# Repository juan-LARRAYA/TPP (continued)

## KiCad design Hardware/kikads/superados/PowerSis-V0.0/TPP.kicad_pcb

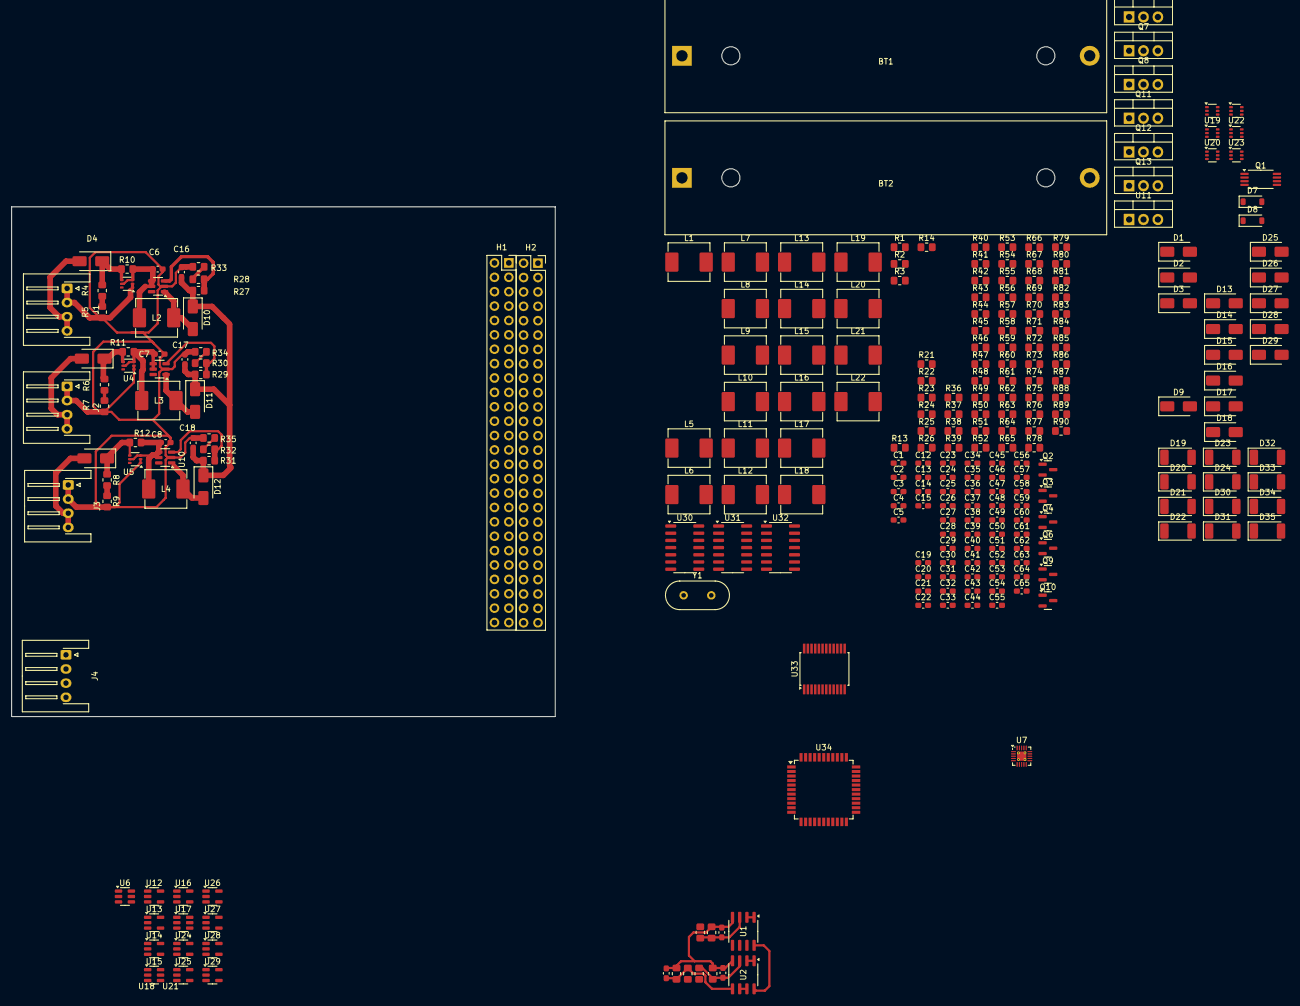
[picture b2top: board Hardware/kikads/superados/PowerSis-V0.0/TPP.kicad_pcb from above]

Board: 2 copper layers, 96.0 x 90.0 mm, 268 parts (0 on the bottom side), 169 nets.

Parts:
BT1, BT2: Battery_Cell; BatteryHolder_MPD_BH-18650-PC2
C1, C2, C3, C4, C5, C15, C19, C20, C21, C22, C23, C24, C25, C26, C27, C28, C29, C30, C31, C44, C45, C46, C47, C48, C49: 100nF; C_0603_1608Metric_Pad1.08x0.95mm_HandSolder
C6, C7, C8, C9, C10, C11, C12, C16, C17, C18, C32, C33, C34, C35, C36, C37, C38, C39, C40, C41, C42, C43: 22uF; C_0603_1608Metric_Pad1.08x0.95mm_HandSolder
C13, C14: 1uF; C_0603_1608Metric_Pad1.08x0.95mm_HandSolder
C50, C51, C52, C53, C54, C55, C56, C57, C58, C59, C60, C61: 10pF; C_0603_1608Metric_Pad1.08x0.95mm_HandSolder
C62, C63, C64, C65: 22pF; C_0603_1608Metric_Pad1.08x0.95mm_HandSolder
D1, D2, D3, D4, D5, D6, D9, D10, D11, D12, D13, D14, D15, D16, D17, D18, D25, D26, D27, D28, D29: CRS08; D_SMA
D7, D8: 1N4148W; D_SOD-123
D19, D20, D21, D22, D23, D24, D30, D31, D32, D33, D34, D35: SMZxxx; D_MELF
H1, H2: Conn_02x26_Odd_Even; PinSocket_2x26_P2.54mm_Vertical
J1, J2, J3, J4: Conn_01x04; JST_XH_S4B-XH-A-1_1x04_P2.50mm_Horizontal
L1, L5, L6, L7, L8, L9, L10: 220uH; L_Abracon_ASPI-0630LR
L2, L3, L4, L11, L12: 22uH; L_Abracon_ASPI-0630LR
L13, L14, L15, L16: 4.7uH; L_Abracon_ASPI-0630LR
L17, L18, L19, L20, L21, L22: 10uH; L_Abracon_ASPI-0630LR
Q1: RU8205G; TSSOP-8_4.4x3mm_P0.65mm
Q2, Q3, Q4, Q6, Q9, Q10: BC817; SOT-23
Q5, Q7, Q8, Q11, Q12, Q13: Q_PMOS_DGS; TO-220-3_Vertical
R1, R2, R3, R22, R26, R36, R38, R42, R44, R46, R48, R55, R56, R57, R58, R59, R60, R61, R62, R63, R64, R65, R66, R67, R68, R69, R70, R71, R72, R73, R74, R75, R76, R77, R78, R79, R80, R81, R82, R83, R84, R85, R86, R87, R88, R89, R90: 1K5; R_0805_2012Metric_Pad1.20x1.40mm_HandSolder
R4, R5, R6, R7, R8, R9, R21, R37: 56K; R_0805_2012Metric_Pad1.20x1.40mm_HandSolder
R10, R11, R12, R49, R50, R51, R52, R53, R54: Rcs; R_0805_2012Metric_Pad1.20x1.40mm_HandSolder
R13, R24: 100; R_0805_2012Metric_Pad1.20x1.40mm_HandSolder
R14: 0.1; R_0805_2012Metric_Pad1.20x1.40mm_HandSolder
R15, R16, R17, R27, R29, R31: 180k; R_0805_2012Metric_Pad1.20x1.40mm_HandSolder
R18, R19, R20, R28, R30, R32, R33, R34, R35: 10k; R_0805_2012Metric_Pad1.20x1.40mm_HandSolder
R23, R25: 0.47; R_0805_2012Metric_Pad1.20x1.40mm_HandSolder
R39: 220K; R_0805_2012Metric_Pad1.20x1.40mm_HandSolder
R40: 1K1; R_0805_2012Metric_Pad1.20x1.40mm_HandSolder
R41, R43, R45, R47: 110K; R_0805_2012Metric_Pad1.20x1.40mm_HandSolder
U1, U2: LM358; SOIC-8_3.9x4.9mm_P1.27mm
U3, U4, U5, U18, U19, U20, U21, U22, U23: INA199xxDCK; SOT-363_SC-70-6
U6, U8, U9, U10, U15, U17: MT3608; SOT-23-6
U7: BQ76905; QFN-20-1EP_3x3mm_P0.4mm_EP1.65x1.65mm_ThermalVias
U11: LM7805_TO220; TO-220-3_Vertical
U12, U13, U14, U16: LM2831YMF; SOT-23-5
U24, U25, U26, U27, U28, U29: SN74LVC1G14DBV; SOT-23-5
U30, U31, U32: 4011; SOIC-14_3.9x8.7mm_P1.27mm
U33: CD74HC4067SM; SSOP-24_5.3x8.2mm_P0.65mm
U34: ATmega1284P-P; TQFP-44_10x10mm_P0.8mm
Y1: Crystal; Crystal_HC49-U_Vertical

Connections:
+3.3V: C58.2, D19.1 (K), H2.27, L19.2
+3.3V Bis: C61.2, D23.1 (K), H2.28, L22.2
+5V: C60.2, D24.1 (K), H2.25, L21.2, R81.1
+5V Bis: C56.2, D21.1 (K), H2.26, L17.2, R82.1
+8V_Aux: C12.1, C15.2, D9.1 (K), R21.1, U11.1 (VI)
+12V: C57.2, D20.1 (K), H1.47, L18.2, R80.1
+24V: C59.2, D22.1 (K), H1.49, L20.2, R79.1
Alert: U7.14 (ALERT), U34.24 (PC2)
Aux +5V: U18.3 (V+), U19.3 (V+), U20.3 (V+), U21.3 (V+), U22.3 (V+), U23.3 (V+), U24.5 (VCC), U25.5 (VCC), U26.5 (VCC), U27.5 (VCC), U28.5 (VCC), U29.5 (VCC), U30.14 (VDD), U31.14 (VDD), U32.14 (VDD)
Batery + In: BT1.1 (+), C16.1, C17.1, C18.1, D7.2 (A), D8.2 (A), D10.1 (K), D11.1 (K), D12.1 (K), H2.45, H2.46, R1.1, R27.1, R29.1, R31.1
Batery + Out: C20.2, C21.2, C22.2, C23.2, C24.2, C25.2, L5.1, L6.1, L7.1, L8.1, L9.1, L10.1
Batery -: BT2.2 (-), C1.1, C4.1, C9.2, C10.2, C11.2, C62.1, C63.1, C64.1, C65.1, R3.1, R13.2, R14.2, R18.2, R19.2, R20.2, U1.4 (V-), U2.4 (V-), U7.11 (VSS), U33.12 (GND), U34.11 (GND), U34.31 (GND)
Batery_middle: BT1.2 (-), BT2.1 (+), R2.1
Enable_+3.3V: U13.4 (EN), U34.16 (PD2)
Enable_+3.3V_Bis: U16.4 (EN), U34.17 (PD3)
Enable_+5V: U12.4 (EN), U34.14 (PD0)
Enable_+5V_Bis: U14.4 (EN), U34.15 (PD1)
Enable_+12V: U17.4 (EN), U34.29 (PC7)
Enable_+24V: U15.4 (EN), U34.28 (PC6)
GND: C3.2, C6.2, C7.2, C8.2, C12.2, C13.1, C14.1, C15.1, C16.2, C17.2, C18.2, C19.1, C20.1, C21.1, C22.1, C23.1, C24.1, C25.1, C26.1, C27.1, C28.1, C29.1, C30.1, C31.1, C32.2, C33.2, C34.2, C35.2, C36.2, C37.2, C38.2, C39.2, C40.2, C41.2, C42.2, C43.2, C44.1, C45.1, C46.1, C47.1, C48.1, C49.1, C50.1, C51.1, C52.1, C53.1, C54.1, C55.1, C56.1, C57.1, C58.1, C59.1, C60.1, C61.1, D13.2 (A), D14.2 (A), D15.2 (A), D17.2 (A), D19.2 (A), D20.2 (A), D21.2 (A), D22.2 (A), D23.2 (A), D24.2 (A), D30.2 (A), D31.2 (A), D32.2 (A), D33.2 (A), D34.2 (A), D35.2 (A), H2.29, H2.30, H2.31, H2.32, J1.1, J1.2, J2.1, J2.2, J3.1, J3.2, J4.1, Q1.2 (D1), Q1.3 (D1), Q2.2 (E), Q3.2 (E), Q4.2 (E), Q6.2 (E), Q9.2 (E), Q10.2 (E), R5.2, R7.2, R9.2, R22.2, R33.2, R34.2, R35.2, R36.2, R38.2, R40.2, R42.2, R44.2, R46.2, R48.2, R85.2, R86.2, R87.2, R88.2, R89.2, R90.2, U3.1 (REF), U3.2 (GND), U4.1 (REF), U4.2 (GND), U5.1 (REF), U5.2 (GND), U6.2 (GND), U8.2 (GND), U9.2 (GND), U10.2 (GND), U11.2 (GND), U12.2 (GND), U13.2 (GND), U14.2 (GND), U15.2 (GND), U16.2 (GND), U17.2 (GND), U18.1 (REF), U18.2 (GND), U19.1 (REF), U19.2 (GND), U20.1 (REF), U20.2 (GND), U21.1 (REF), U21.2 (GND), U22.1 (REF), U22.2 (GND), U23.1 (REF), U23.2 (GND), U24.3 (GND), U25.3 (GND), U26.3 (GND), U27.3 (GND), U28.3 (GND), U29.3 (GND), U30.7 (VSS), U31.7 (VSS), U32.7 (VSS)
MPPT_X_Control: R15.1, U34.19 (PD5)
MPPT_X_Current_Sense: U3.6, U33.9 (I0)
MPPT_X_Voltage_Sense: R4.2, R5.1, U33.8 (I1)
MPPT_Y_Control: R16.1, U34.20 (PD6)
MPPT_Y_Current_Sense: U4.6, U33.7 (I2)
MPPT_Y_Voltage_Sense: R6.2, R7.1, U33.6 (I3)
MPPT_Z_Control: R17.1, U34.21 (PD7)
MPPT_Z_Current_Sense: U5.6, U33.5 (I4)
MPPT_Z_Voltage_Sense: R8.2, R9.1, U33.4 (I5)
unnamed: C44.2, R55.1, U30.6
unnamed: C45.2, R56.1, U31.6
unnamed: C46.2, R57.1, U32.6
unnamed: C47.2, R58.1, U30.13
unnamed: C48.2, R59.1, U31.13
unnamed: C49.2, R60.1, U32.13
unnamed: C3.1, D1.1 (K), D2.1 (K), D3.1 (K), L1.1, U1.8 (V+), U2.8 (V+), U6.4 (EN), U6.5 (IN)
unnamed: D4.1 (K), R4.1, R10.1, U3.4 (+)
unnamed: D5.1 (K), R6.1, R11.1, U4.4 (+)
unnamed: D6.1 (K), R8.1, R12.1, U5.4 (+)
unnamed: D7.1 (K), R23.1
unnamed: D8.1 (K), R25.1
unnamed: D9.2 (A), L1.2, U6.1 (SW)
unnamed: D10.2 (A), L2.2, U8.1 (SW)
unnamed: D11.2 (A), L3.2, U9.1 (SW)
unnamed: D12.2 (A), L4.2, U10.1 (SW)
unnamed: D13.1 (K), L13.1, U13.1 (SW)
unnamed: D14.1 (K), L14.1, U12.1 (SW)
unnamed: D15.1 (K), L15.1, U14.1 (SW)
unnamed: D16.2 (A), L11.2, U15.1 (SW)
unnamed: C42.1, D16.1 (K), R37.1, R51.1, U20.4 (+)
unnamed: D17.1 (K), L16.1, U16.1 (SW)
unnamed: D18.2 (A), L12.2, U17.1 (SW)
unnamed: C43.1, D18.1 (K), R39.1, R54.1, U23.4 (+)
unnamed: D30.1 (K), R79.2, R90.1, U33.3 (I6)
unnamed: D31.1 (K), R80.2, R89.1, U33.2 (I7)
unnamed: D32.1 (K), R81.2, R88.1, U33.23 (I8)
unnamed: D33.1 (K), R82.2, R87.1, U33.22 (I9)
unnamed: D34.1 (K), R83.2, R86.1, U33.21 (I10)
unnamed: D35.1 (K), R84.2, R85.1, U33.20 (I11)
unnamed: Q1.4 (G1), R36.1, U7.10 (CHG)
unnamed: Q1.5 (G2), R26.1, U7.9 (DSG)
unnamed: Q1.1 (S1/D2), Q1.8 (S1/D2)
unnamed: Q1.6 (S2), Q1.7 (S2), R14.1, R24.2, R26.2
unnamed: Q2.1 (B), R62.2
unnamed: Q2.3 (C), R73.2
unnamed: Q3.1 (B), R64.2
unnamed: Q3.3 (C), R74.2
unnamed: Q4.1 (B), R66.2
unnamed: Q4.3 (C), R75.2
unnamed: C54.2, L21.1, Q5.1 (D)
unnamed: Q5.2 (G), R61.2, R73.1
unnamed: Q5.3 (S), R49.2, R61.1, U18.5 (-)
unnamed: Q6.1 (B), R69.2
unnamed: Q6.3 (C), R76.2
unnamed: C52.2, L19.1, Q7.1 (D)
unnamed: Q7.2 (G), R63.2, R74.1
unnamed: Q7.3 (S), R50.2, R63.1, U19.5 (-)
unnamed: C53.2, L20.1, Q8.1 (D)
unnamed: Q8.2 (G), R65.2, R75.1
unnamed: Q8.3 (S), R51.2, R65.1, U20.5 (-)
unnamed: Q9.1 (B), R71.2
unnamed: Q9.3 (C), R77.2
unnamed: Q10.1 (B), R72.2
unnamed: Q10.3 (C), R78.2
unnamed: C50.2, L17.1, Q11.1 (D)
unnamed: Q11.2 (G), R67.2, R76.1
unnamed: Q11.3 (S), R52.2, R67.1, U21.5 (-)
unnamed: C55.2, L22.1, Q12.1 (D)
unnamed: Q12.2 (G), R68.2, R77.1
unnamed: Q12.3 (S), R53.2, R68.1, U22.5 (-)
unnamed: C51.2, L18.1, Q13.1 (D)
unnamed: Q13.2 (G), R70.2, R78.1
unnamed: Q13.3 (S), R54.2, R70.1, U23.5 (-)
unnamed: R55.2, R62.1, U30.2, U30.4
unnamed: R56.2, R64.1, U31.2, U31.4
unnamed: R57.2, R66.1, U32.2, U32.4
unnamed: R58.2, R69.1, U30.9, U30.11
unnamed: R59.2, R71.1, U31.9, U31.11
unnamed: R60.2, R72.1, U32.9, U32.11
unnamed: C9.1, R15.2, R18.1, U1.3 (+)
unnamed: R28.2, R33.1, U1.1, U1.2 (-)
unnamed: C11.1, R17.2, R20.1, U2.3 (+)
unnamed: R32.2, R35.1, U2.1, U2.2 (-)
unnamed: C10.1, R16.2, R19.1, U2.5 (+)
unnamed: R30.2, R34.1, U2.6 (-), U2.7
unnamed: C6.1, L2.1, R10.2, U3.3 (V+), U3.5 (-), U8.4 (EN), U8.5 (IN)
unnamed: C7.1, L3.1, R11.2, U4.3 (V+), U4.5 (-), U9.4 (EN), U9.5 (IN)
unnamed: R21.2, R22.1, U6.3 (FB)
unnamed: C14.2, R25.2, U7.16 (BAT)
unnamed: C13.2, R23.2, U7.17 (REGSRC)
unnamed: C5.1, R13.1, U7.6 (SRN)
unnamed: C5.2, R24.1, U7.7 (SRP)
unnamed: C4.2, R3.2, U7.5 (VC0)
unnamed: C1.2, C2.1, R2.2, U7.1 (VC3A), U7.2 (VC3B), U7.3 (VC2), U7.4 (VC1), U7.19 (VC4A), U7.20 (VC4B)
unnamed: C2.2, R1.2, U7.18 (VC5)
unnamed: R27.2, R28.1, U8.3 (FB)
unnamed: R29.2, R30.1, U9.3 (FB)
unnamed: C8.1, L4.1, R12.2, U5.3 (V+), U5.5 (-), U10.4 (EN), U10.5 (IN)
unnamed: R31.2, R32.1, U10.3 (FB)
unnamed: R41.2, R42.1, U12.3 (FB)
unnamed: C27.2, C32.1, L6.2, U12.5 (VIN)
unnamed: R43.2, R44.1, U13.3 (FB)
unnamed: C26.2, C33.1, L5.2, U13.5 (VIN)
unnamed: R45.2, R46.1, U14.3 (FB)
unnamed: C28.2, C36.1, L7.2, U14.5 (VIN)
unnamed: R37.2, R38.1, U15.3 (FB)
unnamed: C31.2, C34.1, L10.2, L11.1, U15.5 (IN)
unnamed: R47.2, R48.1, U16.3 (FB)
unnamed: C29.2, C37.1, L8.2, U16.5 (VIN)
unnamed: R39.2, R40.1, U17.3 (FB)
unnamed: C30.2, C35.1, L9.2, L12.1, U17.5 (IN)
unnamed: C39.1, L14.2, R41.1, R49.1, U18.4 (+)
unnamed: U18.6, U24.2
unnamed: C38.1, L13.2, R43.1, R50.1, U19.4 (+)
unnamed: U19.6, U25.2
unnamed: U20.6, U26.2
unnamed: C40.1, L15.2, R45.1, R52.1, U21.4 (+)
unnamed: U21.6, U27.2
unnamed: C41.1, L16.2, R47.1, R53.1, U22.4 (+)
unnamed: U22.6, U28.2
unnamed: U23.6, U29.2
unnamed: U24.4, U30.1
unnamed: U25.4, U31.1
unnamed: U26.4, U32.1
unnamed: U27.4, U30.8
unnamed: U28.4, U31.8
unnamed: U29.4, U32.8
unnamed: U33.1 (COM), U34.40 (PA0)
unnamed: U33.10 (S0), U34.39 (PA1)
unnamed: U33.11 (S1), U34.38 (PA2)
unnamed: U33.14 (S2), U34.37 (PA3)
unnamed: U33.13 (S3), U34.36 (PA4)
unnamed: U33.15 (~E), U34.35 (PA5)
unnamed: C64.2, U34.13 (XTAL1), Y1.1
unnamed: C65.2, U34.12 (XTAL2), Y1.2
Ov_Current_+3.3V: U31.3, U31.5, U34.5 (PB4)
Ov_Current_+3.3V_Bis: U31.10, U31.12, U34.6 (PB5)
Ov_Current_+5V: U30.3, U30.5, U34.3 (PB2)
Ov_Current_+5V_Bis: U30.10, U30.12, U34.4 (PB3)
Ov_Current_+12V: U32.10, U32.12, U34.2 (PB1)
Ov_Current_+24V: U32.3, U32.5, U34.1 (PB0)
SCL: H1.41, U7.12 (SCL), U34.23 (PC1)
SDA: H1.43, U7.13 (SDA), U34.22 (PC0)
VccMCU: C62.2, C63.2, D25.1 (K), D26.1 (K), D27.1 (K), D28.1 (K), D29.1 (K), U33.24 (VCC), U34.9 (~RESET), U34.10 (VCC), U34.30 (AVCC)
VregAux: C19.2, D29.2 (A), U11.3 (VO)
Vregout: D28.2 (A), U7.15 (REGOUT)
X_X´_Solar_Cell: D1.2 (A), D4.2 (A), D25.2 (A), J1.3, J1.4
Y_Y´_Solar_Cell: D2.2 (A), D5.2 (A), D26.2 (A), J2.3, J2.4
Z_Z´_Solar_Cell: D3.2 (A), D6.2 (A), D27.2 (A), J3.3, J3.4

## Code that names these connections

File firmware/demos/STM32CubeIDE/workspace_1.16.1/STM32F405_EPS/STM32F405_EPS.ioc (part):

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Mcu.Name=STM32F405RGTx
Mcu.Package=LQFP64
Mcu.UserName=STM32F405RGTx
PA0-WKUP.GPIOParameters=GPIO_Label
PA0-WKUP.GPIO_Label=MPPTYControl
PA0-WKUP.Signal=S_TIM2_CH1_ETR
PA1.GPIOParameters=GPIO_Label
PA1.GPIO_Label=CurrZMPPT
PA1.Signal=ADCx_IN1
PA11.GPIOParameters=GPIO_Label
PA11.GPIO_Label=USB D-
PA11.Mode=Device_Only
PA11.Signal=USB_OTG_FS_DM
PA12.GPIOParameters=GPIO_Label
PA12.GPIO_Label=USB D+
PA12.Mode=Device_Only
PA12.Signal=USB_OTG_FS_DP
PA13.GPIOParameters=GPIO_Label
PA13.GPIO_Label=SWDIO
PA13.Mode=Serial_Wire
PA13.Signal=SYS_JTMS-SWDIO
PA14.GPIOParameters=GPIO_Label
PA14.GPIO_Label=SWCLK
PA14.Mode=Serial_Wire
PA14.Signal=SYS_JTCK-SWCLK
PA2.GPIOParameters=GPIO_Label
PA2.GPIO_Label=VoltZMPPT
PA2.Signal=ADCx_IN2
PA3.GPIOParameters=GPIO_Label
PA3.GPIO_Label=MPPTZControl
PA3.Signal=S_TIM5_CH4
PA4.GPIOParameters=GPIO_Label
PA4.GPIO_Label=Curr5VBis
PA4.Signal=ADCx_IN4
PA5.GPIOParameters=GPIO_Label
PA5.GPIO_Label=Volt5VBis
PA5.Signal=ADCx_IN5
PA6.GPIOParameters=GPIO_Label
PA6.GPIO_Label=Volt3.3V
PA6.Signal=ADCx_IN6
PA7.GPIOParameters=GPIO_Label
PA7.GPIO_Label=Curr3.3V
PA7.Signal=ADCx_IN7
PA8.GPIOParameters=GPIO_Label
PA8.GPIO_Label=SCL-Sat
PA8.Mode=I2C
PA8.Signal=I2C3_SCL
PB0.GPIOParameters=GPIO_Label
PB0.GPIO_Label=Volt3.3VBis
PB0.Signal=ADCx_IN8
PB1.GPIOParameters=GPIO_Label
PB1.GPIO_Label=Curr3.3Vbis
PB1.Signal=ADCx_IN9
PB10.GPIOParameters=GPIO_Label
PB10.GPIO_Label=Enable3.3VBis
PB10.Signal=GPIO_Output
PB11.GPIOParameters=GPIO_Label
PB11.GPIO_Label=Enable3.3V
PB11.Signal=GPIO_Output
PB12.GPIOParameters=GPIO_Label
PB12.GPIO_Label=Enable5VBis
PB12.Signal=GPIO_Output
PB14.GPIOParameters=GPIO_Label
PB14.GPIO_Label=CalEnable
PB14.Signal=GPIO_Output
PB2.GPIOParameters=GPIO_Label
PB2.GPIO_Label=Enable5V
PB2.Signal=GPIO_Output
PB6.GPIOParameters=GPIO_Label
PB6.GPIO_Label=SCL-BMS
PB6.Mode=I2C
PB6.Signal=I2C1_SCL
PB7.GPIOParameters=GPIO_Label
PB7.GPIO_Label=SDA-BMS
PB7.Mode=I2C
PB7.Signal=I2C1_SDA
PB8.GPIOParameters=GPIO_Label
PB8.GPIO_Label=BMS-Alert
PB8.Signal=GPIO_Input
PB9.GPIOParameters=GPIO_Label
PB9.GPIO_Label=MPPTXControl
PB9.Signal=S_TIM4_CH4
PC0.GPIOParameters=GPIO_Label
PC0.GPIO_Label=CurrXMPPT
PC0.Signal=ADCx_IN10
PC1.GPIOParameters=GPIO_Label
PC1.GPIO_Label=VoltXMPPT
PC1.Signal=ADCx_IN11
PC10.GPIOParameters=GPIO_Label
PC10.GPIO_Label=TX
PC10.Mode=Asynchronous
PC10.Signal=UART4_TX
PC11.GPIOParameters=GPIO_Label
PC11.GPIO_Label=RX
PC11.Mode=Asynchronous
PC11.Signal=UART4_RX
PC2.GPIOParameters=GPIO_Label
PC2.GPIO_Label=CurrYMPPT
PC2.Signal=ADCx_IN12
PC3.GPIOParameters=GPIO_Label
PC3.GPIO_Label=VoltYMPPT
PC3.Signal=ADCx_IN13
PC4.GPIOParameters=GPIO_Label
PC4.GPIO_Label=Volt5V
PC4.Signal=ADCx_IN14
PC5.GPIOParameters=GPIO_Label
PC5.GPIO_Label=Curr5V
PC5.Signal=ADCx_IN15
PC9.GPIOParameters=GPIO_Label
PC9.GPIO_Label=SDA-Sat
PC9.Mode=I2C
PC9.Signal=I2C3_SDA
PH0-OSC_IN.Mode=HSE-External-Oscillator
PH0-OSC_IN.Signal=RCC_OSC_IN
PH1-OSC_OUT.Mode=HSE-External-Oscillator
PH1-OSC_OUT.Signal=RCC_OSC_OUT
RCC.HSE_VALUE=8000000
RCC.SYSCLKFreq_VALUE=168000000
RCC.SYSCLKSource=RCC_SYSCLKSOURCE_PLLCLK
board=custom

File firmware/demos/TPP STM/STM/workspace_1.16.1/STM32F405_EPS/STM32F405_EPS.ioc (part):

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Mcu.Name=STM32F405RGTx
Mcu.Package=LQFP64
Mcu.UserName=STM32F405RGTx
PA0-WKUP.GPIOParameters=GPIO_Label
PA0-WKUP.GPIO_Label=MPPTYControl
PA0-WKUP.Signal=S_TIM2_CH1_ETR
PA1.GPIOParameters=GPIO_PuPd,GPIO_Label,GPIO_Mode
PA1.GPIO_Label=MPPZ_CUR
PA1.GPIO_Mode=GPIO_MODE_ANALOG
PA1.GPIO_PuPd=GPIO_NOPULL
PA1.Signal=ADCx_IN1
PA13.GPIOParameters=GPIO_Label
PA13.GPIO_Label=SWDIO
PA13.Mode=Serial_Wire
PA13.Signal=SYS_JTMS-SWDIO
PA14.GPIOParameters=GPIO_Label
PA14.GPIO_Label=SWCLK
PA14.Mode=Serial_Wire
PA14.Signal=SYS_JTCK-SWCLK
PA2.GPIOParameters=GPIO_PuPd,GPIO_Label,GPIO_Mode
PA2.GPIO_Label=MPPZ_VOL
PA2.GPIO_Mode=GPIO_MODE_ANALOG
PA2.GPIO_PuPd=GPIO_NOPULL
PA2.Signal=ADCx_IN2
PA3.GPIOParameters=GPIO_Label
PA3.GPIO_Label=MPPTZControl
PA3.Signal=S_TIM5_CH4
PA4.GPIOParameters=GPIO_PuPd,GPIO_Label,GPIO_Mode
PA4.GPIO_Label=CUR_5BIS
PA4.GPIO_Mode=GPIO_MODE_ANALOG
PA4.GPIO_PuPd=GPIO_NOPULL
PA4.Signal=ADCx_IN4
PA5.GPIOParameters=GPIO_PuPd,GPIO_Label,GPIO_Mode
PA5.GPIO_Label=VOL_5BIS
PA5.GPIO_Mode=GPIO_MODE_ANALOG
PA5.GPIO_PuPd=GPIO_NOPULL
PA5.Signal=ADCx_IN5
PA6.GPIOParameters=GPIO_PuPd,GPIO_Label,GPIO_Mode
PA6.GPIO_Label=VOL_3.3V
PA6.GPIO_Mode=GPIO_MODE_ANALOG
PA6.GPIO_PuPd=GPIO_NOPULL
PA6.Signal=ADCx_IN6
PA7.GPIOParameters=GPIO_PuPd,GPIO_Label,GPIO_Mode
PA7.GPIO_Label=CUR_3.3V
PA7.GPIO_Mode=GPIO_MODE_ANALOG
PA7.GPIO_PuPd=GPIO_NOPULL
PA7.Signal=ADCx_IN7
PA8.GPIOParameters=GPIO_Label,GPIO_Pu
PA8.GPIO_Label=SCL_I2C_COM
PA8.GPIO_Pu=GPIO_PULLUP
PA8.Mode=I2C
PA8.Signal=I2C3_SCL
PA9.GPIOParameters=GPIO_PuPd,GPIO_Label
PA9.GPIO_Label=EnableBatOut
PA9.GPIO_PuPd=GPIO_PULLUP
PA9.Signal=GPIO_Output
PB0.GPIOParameters=GPIO_Label
PB0.GPIO_Label=CELL_MENOS
PB0.Signal=ADCx_IN8
PB11.GPIOParameters=GPIO_PuPd,GPIO_Label
PB11.GPIO_Label=Enable3.3V
PB11.GPIO_PuPd=GPIO_PULLUP
PB11.Signal=GPIO_Output
PB12.GPIOParameters=GPIO_PuPd,GPIO_Label
PB12.GPIO_Label=Enable5VBis
PB12.GPIO_PuPd=GPIO_PULLUP
PB12.Signal=GPIO_Output
PB14.GPIOParameters=GPIO_PuPd,GPIO_Label
PB14.GPIO_Label=EnableCalefactor 
PB14.GPIO_PuPd=GPIO_PULLUP
PB14.Signal=GPIO_Output
PB6.GPIOParameters=GPIO_Speed,GPIO_Label,GPIO_Pu,GPIO_Mode
PB6.GPIO_Label=SCL_I2C_BMS
PB6.GPIO_Mode=GPIO_MODE_AF_OD
PB6.GPIO_Pu=GPIO_NOPULL
PB6.GPIO_Speed=GPIO_SPEED_FREQ_VERY_HIGH
PB6.Mode=I2C
PB6.Signal=I2C1_SCL
PB7.GPIOParameters=GPIO_Speed,GPIO_Label,GPIO_Pu
PB7.GPIO_Label=SDA_I2C_BMS
PB7.GPIO_Pu=GPIO_NOPULL
PB7.GPIO_Speed=GPIO_SPEED_FREQ_VERY_HIGH
PB7.Mode=I2C
PB7.Signal=I2C1_SDA
PB8.GPIOParameters=GPIO_PuPd,GPIO_Label
PB8.GPIO_Label=BMS-Alert
PB8.GPIO_PuPd=GPIO_PULLUP
PB8.Signal=GPIO_Input
PB9.GPIOParameters=GPIO_Label
PB9.GPIO_Label=MPPTXControl
PB9.Signal=S_TIM4_CH4
PC0.GPIOParameters=GPIO_PuPd,GPIO_Label,GPIO_Mode
PC0.GPIO_Label=MPPX_CUR
PC0.GPIO_Mode=GPIO_MODE_ANALOG
PC0.GPIO_PuPd=GPIO_NOPULL
PC0.Signal=ADCx_IN10
PC1.GPIOParameters=GPIO_PuPd,GPIO_Label,GPIO_Mode
PC1.GPIO_Label=MPPX_VOL
PC1.GPIO_Mode=GPIO_MODE_ANALOG
PC1.GPIO_PuPd=GPIO_NOPULL
PC1.Signal=ADCx_IN11
PC10.GPIOParameters=GPIO_PuPd,GPIO_Label
PC10.GPIO_Label=TX
PC10.GPIO_PuPd=GPIO_PULLUP
PC10.Mode=Asynchronous
PC10.Signal=UART4_TX
PC11.GPIOParameters=GPIO_PuPd,GPIO_Label
PC11.GPIO_Label=RX
PC11.GPIO_PuPd=GPIO_PULLUP
PC11.Mode=Asynchronous
PC11.Signal=UART4_RX
PC2.GPIOParameters=GPIO_PuPd,GPIO_Label,GPIO_Mode
PC2.GPIO_Label=MPPY_CUR
PC2.GPIO_Mode=GPIO_MODE_ANALOG
PC2.GPIO_PuPd=GPIO_NOPULL
PC2.Signal=ADCx_IN12
PC3.GPIOParameters=GPIO_PuPd,GPIO_Label,GPIO_Mode
PC3.GPIO_Label=MPPY_VOL
PC3.GPIO_Mode=GPIO_MODE_ANALOG
PC3.GPIO_PuPd=GPIO_NOPULL
PC3.Signal=ADCx_IN13
PC4.GPIOParameters=GPIO_Label
PC4.GPIO_Label=CELL_MAS
PC4.Signal=ADCx_IN14
PC5.GPIOParameters=GPIO_Label
PC5.GPIO_Label=CURR_BQ29330
PC5.Signal=ADCx_IN15
PC6.Signal=S_TIM3_CH1
PC9.GPIOParameters=GPIO_Label,GPIO_Pu
PC9.GPIO_Label=SDA_I2C_COM
PC9.GPIO_Pu=GPIO_PULLUP
PC9.Mode=I2C
PC9.Signal=I2C3_SDA
PH0-OSC_IN.Mode=HSE-External-Oscillator
PH0-OSC_IN.Signal=RCC_OSC_IN
PH1-OSC_OUT.Mode=HSE-External-Oscillator
PH1-OSC_OUT.Signal=RCC_OSC_OUT
RCC.HSE_VALUE=8000000
RCC.SYSCLKFreq_VALUE=32000000
RCC.SYSCLKSource=RCC_SYSCLKSOURCE_PLLCLK
board=custom

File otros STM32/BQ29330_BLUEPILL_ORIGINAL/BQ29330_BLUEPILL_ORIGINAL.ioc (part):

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Mcu.Name=STM32F103C(8-B)Tx
Mcu.Package=LQFP48
Mcu.UserName=STM32F103C8Tx
PA0-WKUP.GPIOParameters=GPIO_Label
PA0-WKUP.GPIO_Label=Curr_bats
PA0-WKUP.Signal=ADCx_IN0
PA1.GPIOParameters=GPIO_Label
PA1.GPIO_Label=Vbat1
PA1.Signal=ADCx_IN1
PA10.Mode=Asynchronous
PA10.Signal=USART1_RX
PA11.Mode=Device
PA11.Signal=USB_DM
PA12.Mode=Device
PA12.Signal=USB_DP
PA13.Mode=Serial_Wire
PA13.Signal=SYS_JTMS-SWDIO
PA14.Mode=Serial_Wire
PA14.Signal=SYS_JTCK-SWCLK
PA2.GPIOParameters=GPIO_Label
PA2.GPIO_Label=Vbat2
PA2.Signal=ADCx_IN2
PA8.GPIOParameters=GPIO_Label
PA8.GPIO_Label=WDI_32KHz
PA8.Signal=S_TIM1_CH1
PA9.Mode=Asynchronous
PA9.Signal=USART1_TX
PB10.Mode=I2C
PB10.Signal=I2C2_SCL
PB11.Mode=I2C
PB11.Signal=I2C2_SDA
PB12.Signal=GPIO_Analog
PB6.Mode=I2C
PB6.Signal=I2C1_SCL
PB7.Mode=I2C
PB7.Signal=I2C1_SDA
PC13-TAMPER-RTC.GPIOParameters=GPIO_Label
PC13-TAMPER-RTC.GPIO_Label=activador
PC13-TAMPER-RTC.Signal=GPIO_Output
PD0-OSC_IN.Mode=HSE-External-Oscillator
PD0-OSC_IN.Signal=RCC_OSC_IN
PD1-OSC_OUT.Mode=HSE-External-Oscillator
PD1-OSC_OUT.Signal=RCC_OSC_OUT
RCC.SYSCLKFreq_VALUE=48000000
RCC.SYSCLKSource=RCC_SYSCLKSOURCE_PLLCLK
board=custom

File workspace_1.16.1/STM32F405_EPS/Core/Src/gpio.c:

/* USER CODE BEGIN Header */
/**
  ******************************************************************************
  * @file    gpio.c
  * @brief   This file provides code for the configuration
  *          of all used GPIO pins.
  ******************************************************************************
  * @attention
  *
  * Copyright (c) 2025 STMicroelectronics.
  * All rights reserved.
  *
  * This software is licensed under terms that can be found in the LICENSE file
  * in the root directory of this software component.
  * If no LICENSE file comes with this software, it is provided AS-IS.
  *
  ******************************************************************************
  */
/* USER CODE END Header */

/* Includes ------------------------------------------------------------------*/
#include "gpio.h"

/* USER CODE BEGIN 0 */

/* USER CODE END 0 */

/*----------------------------------------------------------------------------*/
/* Configure GPIO                                                             */
/*----------------------------------------------------------------------------*/
/* USER CODE BEGIN 1 */

/* USER CODE END 1 */

/** Configure pins as
        * Analog
        * Input
        * Output
        * EVENT_OUT
        * EXTI
        * Free pins are configured automatically as Analog (this feature is enabled through
        * the Code Generation settings)
*/
void MX_GPIO_Init(void)
{

  GPIO_InitTypeDef GPIO_InitStruct = {0};

  /* GPIO Ports Clock Enable */
  __HAL_RCC_GPIOC_CLK_ENABLE();
  __HAL_RCC_GPIOH_CLK_ENABLE();
  __HAL_RCC_GPIOA_CLK_ENABLE();
  __HAL_RCC_GPIOB_CLK_ENABLE();
  __HAL_RCC_GPIOD_CLK_ENABLE();

  /*Configure GPIO pin Output Level */
  HAL_GPIO_WritePin(GPIOB, Enable3_3V_Pin|Enable5VBis_Pin|EnableCalefactor_Pin, GPIO_PIN_RESET);

  /*Configure GPIO pin Output Level */
  HAL_GPIO_WritePin(EnableBatOut_GPIO_Port, EnableBatOut_Pin, GPIO_PIN_RESET);

  /*Configure GPIO pins : PC13 PC14 PC15 PC7
                           PC8 PC12 */
  GPIO_InitStruct.Pin = GPIO_PIN_13|GPIO_PIN_14|GPIO_PIN_15|GPIO_PIN_7
                          |GPIO_PIN_8|GPIO_PIN_12;
  GPIO_InitStruct.Mode = GPIO_MODE_ANALOG;
  GPIO_InitStruct.Pull = GPIO_NOPULL;
  HAL_GPIO_Init(GPIOC, &GPIO_InitStruct);

  /*Configure GPIO pins : PB1 PB2 PB10 PB13
                           PB15 PB3 PB4 PB5 */
  GPIO_InitStruct.Pin = GPIO_PIN_1|GPIO_PIN_2|GPIO_PIN_10|GPIO_PIN_13
                          |GPIO_PIN_15|GPIO_PIN_3|GPIO_PIN_4|GPIO_PIN_5;
  GPIO_InitStruct.Mode = GPIO_MODE_ANALOG;
  GPIO_InitStruct.Pull = GPIO_NOPULL;
  HAL_GPIO_Init(GPIOB, &GPIO_InitStruct);

  /*Configure GPIO pins : PBPin PBPin PBPin */
  GPIO_InitStruct.Pin = Enable3_3V_Pin|Enable5VBis_Pin|EnableCalefactor_Pin;
  GPIO_InitStruct.Mode = GPIO_MODE_OUTPUT_PP;
  GPIO_InitStruct.Pull = GPIO_PULLUP;
  GPIO_InitStruct.Speed = GPIO_SPEED_FREQ_LOW;
  HAL_GPIO_Init(GPIOB, &GPIO_InitStruct);

  /*Configure GPIO pin : PtPin */
  GPIO_InitStruct.Pin = EnableBatOut_Pin;
  GPIO_InitStruct.Mode = GPIO_MODE_OUTPUT_PP;
  GPIO_InitStruct.Pull = GPIO_PULLUP;
  GPIO_InitStruct.Speed = GPIO_SPEED_FREQ_LOW;
  HAL_GPIO_Init(EnableBatOut_GPIO_Port, &GPIO_InitStruct);

  /*Configure GPIO pins : PA10 PA15 */
  GPIO_InitStruct.Pin = GPIO_PIN_10|GPIO_PIN_15;
  GPIO_InitStruct.Mode = GPIO_MODE_ANALOG;
  GPIO_InitStruct.Pull = GPIO_NOPULL;
  HAL_GPIO_Init(GPIOA, &GPIO_InitStruct);

  /*Configure GPIO pin : PD2 */
  GPIO_InitStruct.Pin = GPIO_PIN_2;
  GPIO_InitStruct.Mode = GPIO_MODE_ANALOG;
  GPIO_InitStruct.Pull = GPIO_NOPULL;
  HAL_GPIO_Init(GPIOD, &GPIO_InitStruct);

  /*Configure GPIO pin : PtPin */
  GPIO_InitStruct.Pin = BMS_Alert_Pin;
  GPIO_InitStruct.Mode = GPIO_MODE_INPUT;
  GPIO_InitStruct.Pull = GPIO_PULLUP;
  HAL_GPIO_Init(BMS_Alert_GPIO_Port, &GPIO_InitStruct);

}

/* USER CODE BEGIN 2 */

/* USER CODE END 2 */

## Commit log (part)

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2024-09-26 Agregados archivos desde la carpeta 'folder'
2024-10-26 Add files via upload
    Primera version del diseño realizado, previo a ordenar los componentes y a rutear
2024-11-17 Añadir tres carpetas desde rutas diferentes
2024-11-17 cambio en las estructuras de los directorios
2024-11-18 subiendo los programas que hice en el STCubeIde
2024-12-05 actualizacion del repositorio a solo codigo para evitar problemas de carpetas en multiples lugares del SO
2024-12-10 cambios de configuracion en el entorno st cube ide y trabajo en el archivo de la bluepil
2024-12-13 cambios importantes en los drivers y en la configuracion del entorno(nose si se guarda en alguno de los archivos del proyecto)
2024-12-14 agregue un nuevo proyecto para tener la copia del stm32
2024-12-24 se agrego el mppt a la version 405
2024-12-25 bms y pdu agregados
2024-12-25 cambio en la organizacion de lar carpetas
2024-12-25 cambio en carpetas
2025-01-05 cambios realizados con diego
2025-01-12 ultimas modificaciones antes de hacer andar el BMS
2025-03-01 01-03-2025 pudimos escribir todavia no emprolijamos el codigo
2025-03-02 restructuracion de carpetas
2025-03-02 modularizacion del cododigo, creacion de estructs para ejex,y,z y las fuentes de 5,5b,3,3b
2025-03-03 creacion de estructuras de datos y modularizacion de las funciones del BMS
2025-03-03 comunicaion y lectura de los parametros del bq al arduino usando i2c en ambas comunicaciones
2025-03-09 pruebas y mejoras de mqtt
2025-03-27 ahora anda el adc uso solo el adc1 para las 14 entradas
2025-03-30 agrego el to do y cambio las funciones para imprimir
2025-04-13 domingo 20250413 pruebas mppt
2025-05-04 cambios en bms y frec de sw para mqtt
2025-05-10 agregue los arduinos para el ina y para leer i2c y devolcer serial
2025-05-12 cambio de bms al 29330 y emprolijamiento de configo usando functiones
2025-05-13 se borraron salidas que no se usaban del bms viejo y de los pdu quemados y se creo el proyecto para probar el bms 29330 con la bluepill
2025-05-18 funciones de i2c funcionando par ael 29330
2025-05-25 cambios hechos con nico el 18 de mayo 2025
2025-05-26 agregamos adc y coulomb counter al programa en arduino
2025-06-02 domingo de pruebas con nico falta modularizar el bms anda
2025-06-16 funciona la com con el ina y stm32 agrego estructura base del proyecto para el informe
2025-06-16 emprolije el codigo del blupill original
2025-06-21 viendo git con diego y aniadimos cambios todo ok funcionando ina219 actualizado con coulomb counter
2025-06-23 cambios en original y agregamos libreria piserial para crear un excel y para ver el monitor serial desde la cursor
2025-06-28 todo modularizando y andando para hacer la carga y descarga
2025-07-16 agregue al f405 todas las funcionalidades que teniamos en la bluepill, se estan rompiendo los archivos ina219 al compilar y no entiendo porque quizas tenga que ver con la libreria de HAL
2025-07-17 Update build files to compile INA219 driver
2025-12-02 feat: Add .gitignore to exclude build and IDE files
2025-12-02 feat: Finalizar la reorganización del repositorio y mover todo el código a la carpeta firmware
2025-12-07 filmware final
